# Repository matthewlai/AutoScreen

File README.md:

# AutoScreen
Device to automatically lower motorised projector screen to a set height through IR when power is applied, and raise it when power is removed.

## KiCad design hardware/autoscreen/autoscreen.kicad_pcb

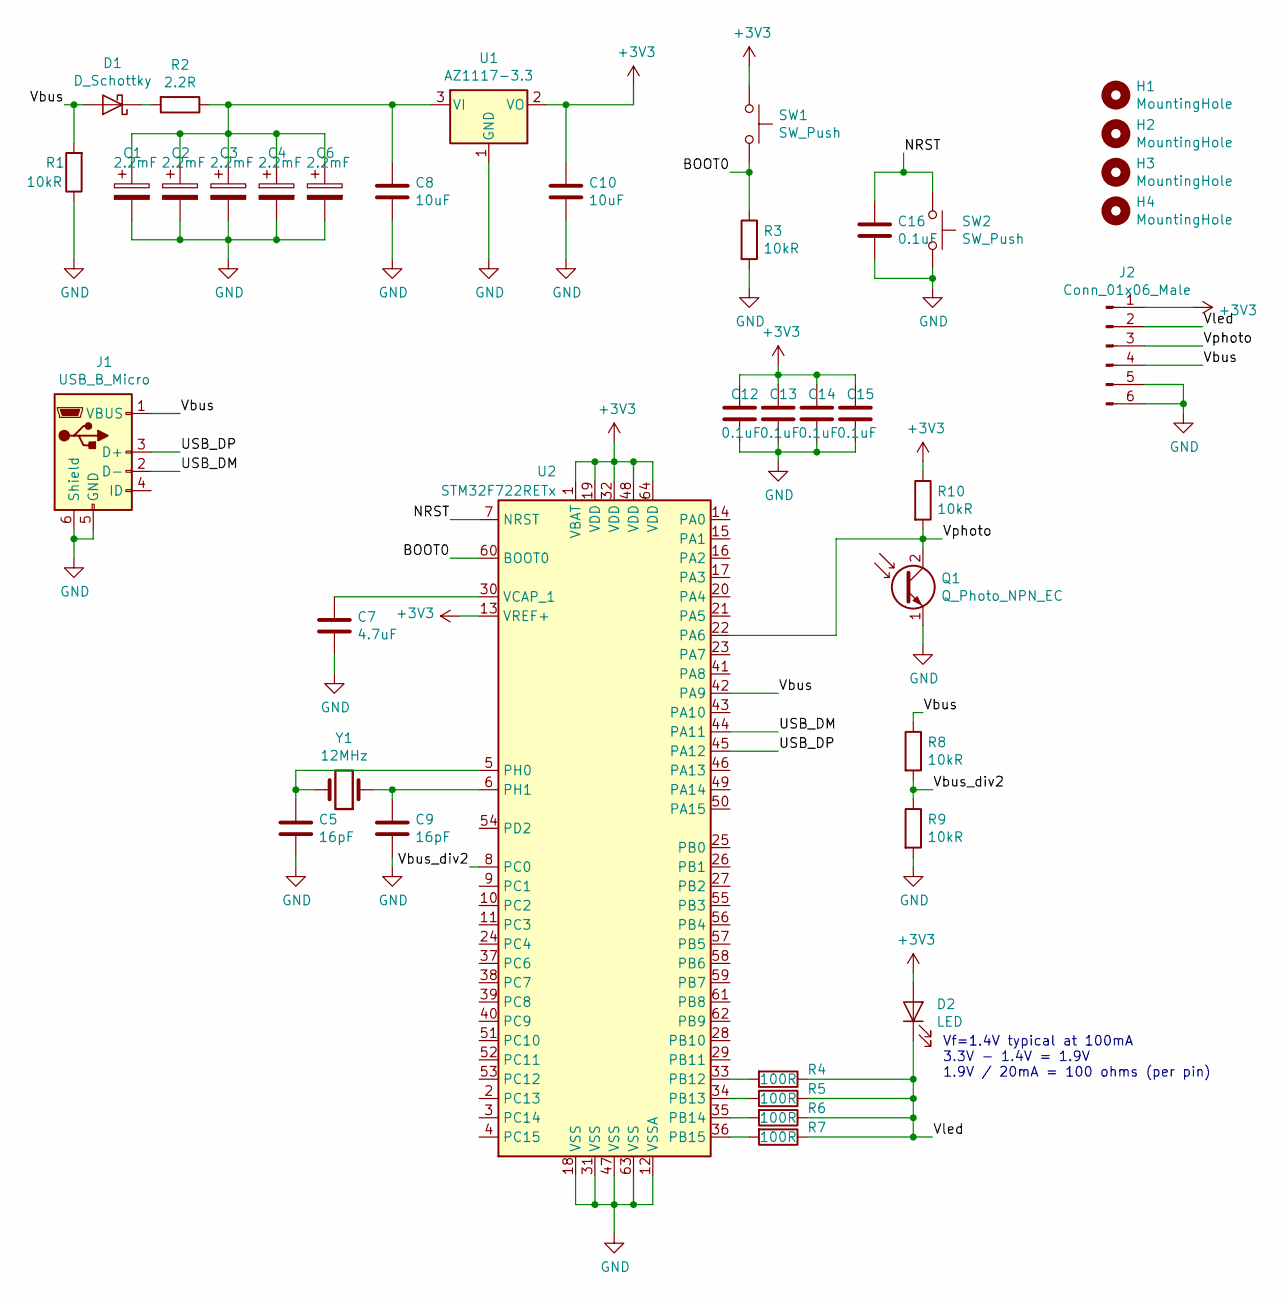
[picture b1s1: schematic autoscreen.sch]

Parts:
C1, C2, C3, C4, C6: 2.2mF; CP_Radial_D10.0mm_P5.00mm
C5, C9: 16pF; C_0805_2012Metric_Pad1.15x1.40mm_HandSolder
C7: 4.7uF; C_0805_2012Metric_Pad1.15x1.40mm_HandSolder
C8, C10: 10uF; C_1206_3216Metric_Pad1.42x1.75mm_HandSolder
C12, C13, C14, C15, C16: 0.1uF; C_0805_2012Metric_Pad1.15x1.40mm_HandSolder
D1: D_Schottky; D_1206_3216Metric_Pad1.42x1.75mm_HandSolder
D2: LED; LED_D5.0mm_Horizontal_O1.27mm_Z3.0mm_IRBlack
H1, H2, H3, H4: MountingHole; MountingHole_3.2mm_M3
J1: USB_B_Micro; USB_Micro-B_Molex-105017-0001
J2: Conn_01x06_Male; PinHeader_1x06_P2.54mm_Vertical
Q1: Q_Photo_NPN_EC; LED_D5.0mm_Horizontal_O1.27mm_Z3.0mm
R1, R3, R8, R9, R10: 10kR; R_0805_2012Metric_Pad1.15x1.40mm_HandSolder
R2: 2.2R; R_0805_2012Metric_Pad1.15x1.40mm_HandSolder
R4, R5, R6, R7: 100R; R_0805_2012Metric_Pad1.15x1.40mm_HandSolder
SW1, SW2: SW_Push; SW_SPST_B3S-1000
U1: AZ1117-3.3; SOT-223-3_TabPin2
U2: STM32F722RETx; LQFP-64_10x10mm_P0.5mm
Y1: 12MHz; Crystal_SMD_HC49-SD_HandSoldering

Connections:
+3V3: C10.1, C12.1, C13.1, C14.1, C15.1, D2.2 (A), J2.1, R10.1, SW1.1, U1.2 (VO), U2.1 (VBAT), U2.13 (VREF+), U2.19 (VDD), U2.32 (VDD), U2.48 (VDD), U2.64 (VDD)
/BOOT0: R3.1, SW1.2, U2.60 (BOOT0)
/NRST: C16.1, SW2.1, U2.7 (NRST)
/USB_DM: J1.2 (D-), U2.44 (PA11)
/USB_DP: J1.3 (D+), U2.45 (PA12)
/Vbus: D1.2 (A), J1.1 (VBUS), J2.4, R1.2, R8.1, U2.42 (PA9)
/Vbus_div2: R8.2, R9.1, U2.8 (PC0)
/Vled: D2.1 (K), J2.2, R4.1, R5.1, R6.1, R7.1
/Vphoto: J2.3, Q1.2 (C), R10.2, U2.22 (PA6)
GND: C1.2, C2.2, C3.2, C4.2, C5.2, C6.2, C7.2, C8.2, C9.2, C10.2, C12.2, C13.2, C14.2, C15.2, C16.2, J1.5 (GND), J1.6 (Shield), J2.5, J2.6, Q1.1 (E), R1.1, R3.2, R9.2, SW2.2, U1.1 (GND), U2.12 (VSSA), U2.18 (VSS), U2.31 (VSS), U2.47 (VSS), U2.63 (VSS)
unnamed: C1.1, C2.1, C3.1, C4.1, C6.1, C8.1, R2.1, U1.3 (VI)
unnamed: C5.1, U2.5 (PH0), Y1.2
unnamed: C7.1, U2.30 (VCAP_1)
unnamed: C9.1, U2.6 (PH1), Y1.1
unnamed: D1.1 (K), R2.2
unnamed: R4.2, U2.33 (PB12)
unnamed: R5.2, U2.34 (PB13)
unnamed: R6.2, U2.35 (PB14)
unnamed: R7.2, U2.36 (PB15)

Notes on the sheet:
Vf=1.4V typical at 100mA 3.3V - 1.4V = 1.9V 1.9V / 20mA = 100 ohms (per pin)

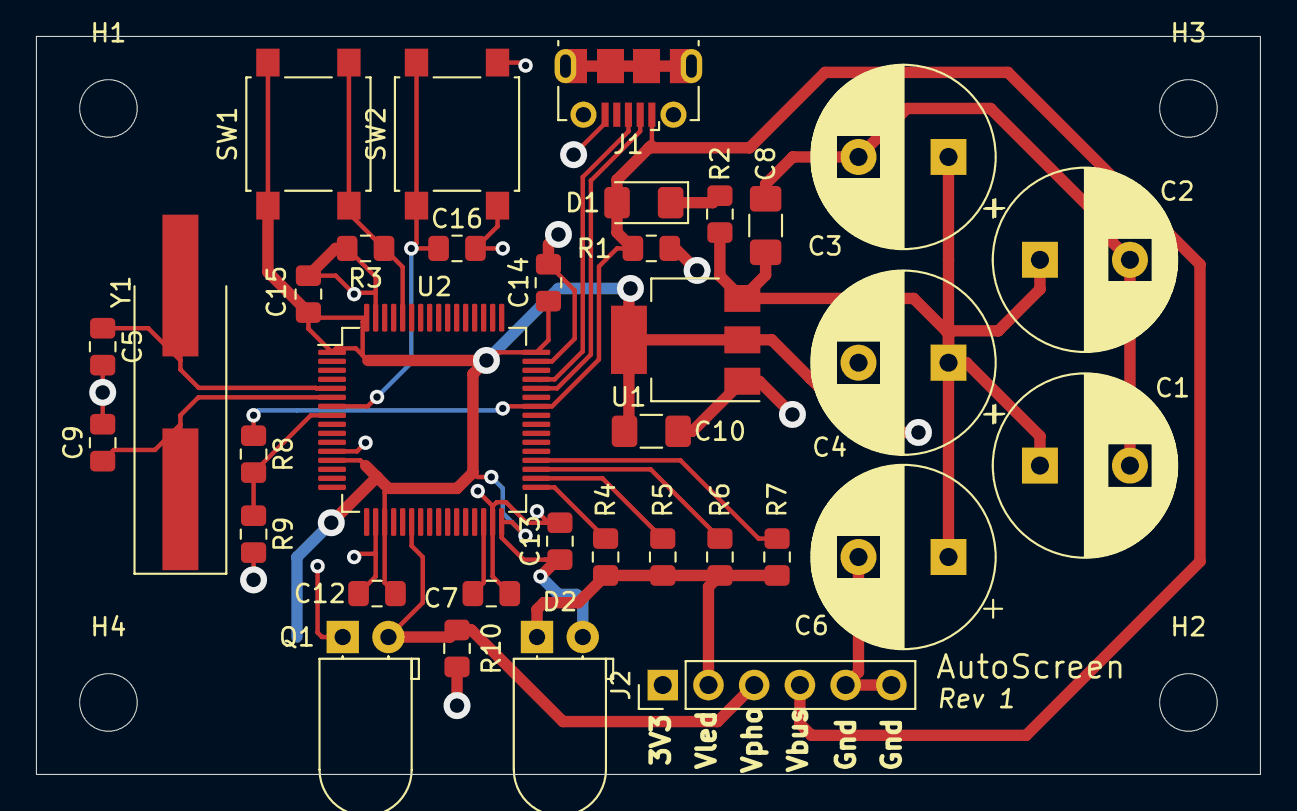
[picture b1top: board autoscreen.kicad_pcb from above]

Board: 2 copper layers, 68.0 x 41.0 mm, 39 parts (0 on the bottom side), 19 nets.

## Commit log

2019-09-08 Hardware rev 1
2019-09-08 Added fab files
2019-09-08 Moved passives away from the TQFP chip for easier rework, and added silkscreen ID
2019-09-27 Added firmware
2019-10-15 Updated input resistor value to limit inrush current
